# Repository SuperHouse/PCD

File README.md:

PiCAN Display Hat for Raspberry Pi
==================================
Designed by Jonathan Oxer <jon@oxer.com.au>

FEATURES
--------

Supply power via CAN bus, screw terminals, 2.1mm DC jack, or the
PoE header on Raspberry Pi 3 B+. Regulates down to 5V to supply the
Raspberry Pi.

TCAN332 + MCP2515 based CAN bus interface.

0.96" I2C OLED.

INSTALLATION
------------
The design is saved as an EAGLE project. EAGLE PCB design software is
available from www.cadsoftusa.com free for non-commercial use. To use
this project download it and place the directory containing these files
into the "eagle" directory on your computer. Then open EAGLE and
navigate to the project.

DISTRIBUTION
------------
The specific terms of distribution of this project are governed by the
license referenced below.

LICENSE
-------
Licensed under the TAPR Open Hardware License (www.tapr.org/OHL).
The "license" folder within this repository also contains a copy of
this license in plain text format.

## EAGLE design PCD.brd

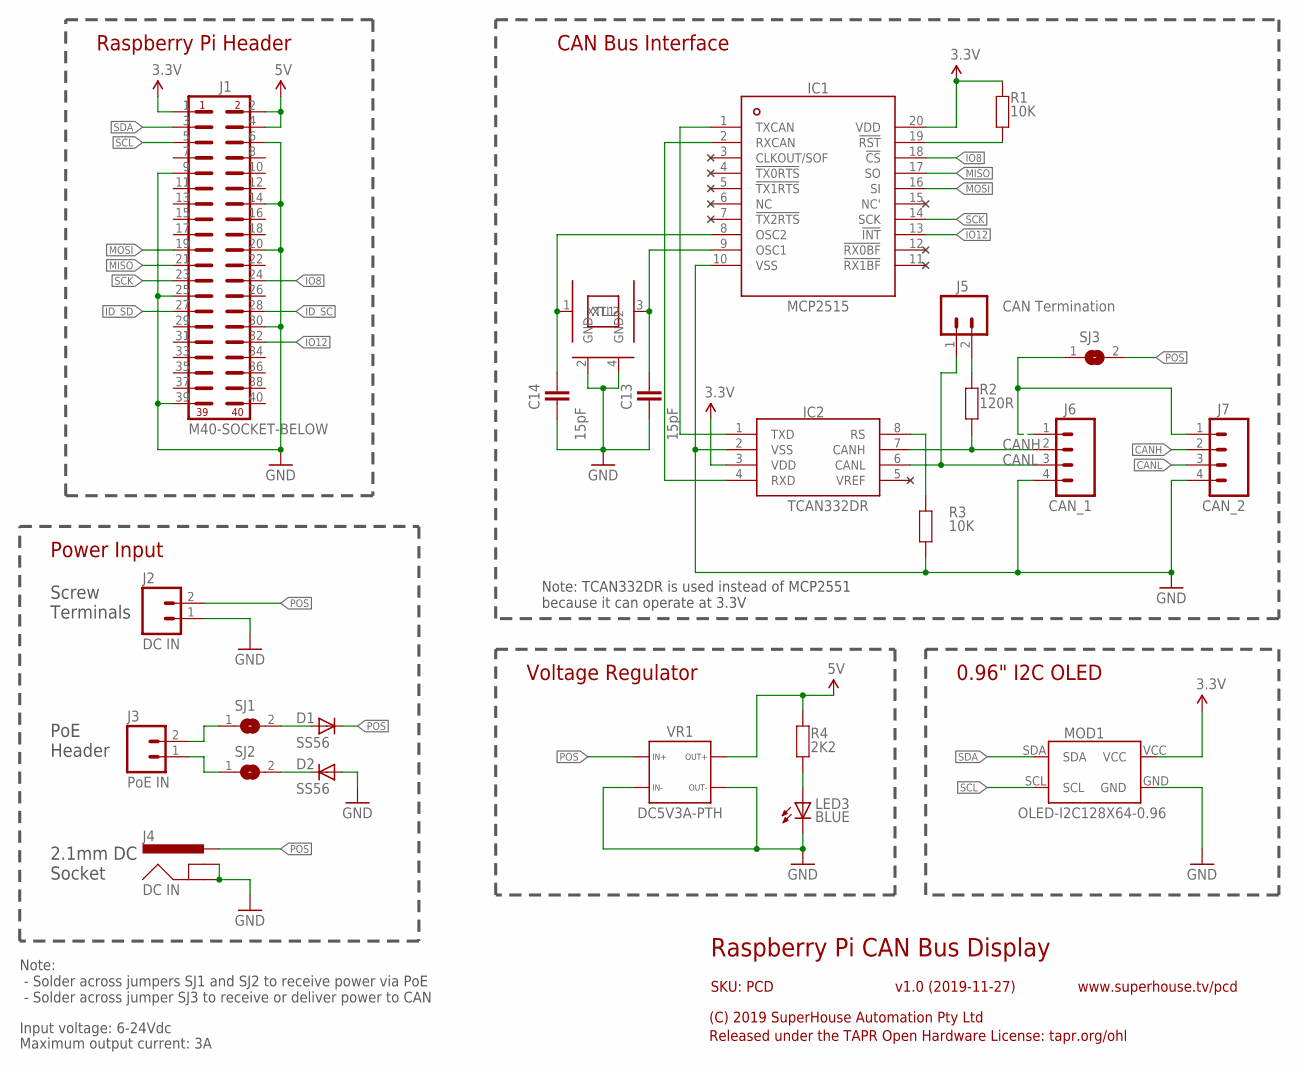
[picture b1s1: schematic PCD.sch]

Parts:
C13, C14: 15pF; C0603
D1, D2: SS56; SMA-DIODE
IC1: MCP2515; TSSOP20
IC2: TCAN332DR; SO08
J1: M40-SOCKET-BELOW; 2X20-S-BELOW
J2: DC IN; SCREWTERMINAL-3.5MM-2
J3: PoE IN; 1X02-S-BELOW
J4: DC IN; POWER_JACK_SLOTS
J5: CAN Termination; 1X02-P
J6: CAN_1; 1X04-P
J7: CAN_2; 1X04-P
LED3: BLUE; LED-0603
MOD1: OLED-I2C128X64-0.96; OLED-128X64-0.96
R1, R3: 10K; R0603
R2: 120R; R0603
R4: 2K2; R0603
SJ1, SJ2, SJ3: SJN; SJ
VR1: DC5V3A-PTH
XTL3: 16MHz; CRYSTAL-SMD-3X2

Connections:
3.3V: IC1.20 (VDD), IC2.3 (VDD), J1.1, MOD1.VCC, R1.2
5V: J1.2, J1.4, R4.1, VR1.3A (3), VR1.3B (3)
CANH: IC2.7 (CANH), J6.2, J7.2, R2.1
CANL: IC2.6 (CANL), J5.1, J6.3, J7.3
CAN_PWR: J6.1, J7.1, SJ3.1
GND: C13.1, C14.1, D2.A, IC1.10 (VSS), IC2.2 (VSS), J1.6, J1.9, J1.14, J1.20, J1.25, J1.30, J1.39, J2.1, J4.GND, J4.GNDBREAK, J6.4, J7.4, LED3.C, MOD1.GND, R3.1, VR1.1A (1), VR1.1B (1), VR1.4A (4), VR1.4B (4), XTL3.2 (GND), XTL3.4 (GND2)
ID_SC: J1.28
ID_SD: J1.27
IO8: IC1.18 (!CS), J1.24
IO12: IC1.13 (!INT), J1.32
MISO: IC1.17 (SO), J1.21
MOSI: IC1.16 (SI), J1.19
unnamed: J3.1, SJ2.1
unnamed: J3.2, SJ1.1
unnamed: J5.2, R2.2
unnamed: D1.A, SJ1.2
unnamed: D2.C, SJ2.2
unnamed: IC2.8 (RS), R3.2
unnamed: IC1.1 (TXCAN), IC2.1 (TXD)
unnamed: IC1.2 (RXCAN), IC2.4 (RXD)
unnamed: C13.2, IC1.9 (OSC1), XTL3.3 (XTL2)
unnamed: C14.2, IC1.8 (OSC2), XTL3.1 (XTL1)
unnamed: IC1.19 (!RST), R1.1
unnamed: LED3.A, R4.2
POS: D1.C, J2.2, J4.PWR, SJ3.2, VR1.2A (2), VR1.2B (2)
SCK: IC1.14 (SCK), J1.23
SCL: J1.5, MOD1.SCL
SDA: J1.3, MOD1.SDA

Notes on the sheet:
Raspberry Pi CAN Bus Display
v1.0 (2019-11-27)
(C) 2019 SuperHouse Automation Pty Ltd
Released under the TAPR Open Hardware License: tapr.org/ohl
www.superhouse.tv/pcd
SKU: PCD
Raspberry Pi Header
Input voltage: 6-24Vdc
Maximum output current: 3A
Screw Terminals
PoE Header
2.1mm DC Socket
Power Input
Voltage Regulator
Note: - Solder across jumpers SJ1 and SJ2 to receive power via PoE - Solder across jumper SJ3 to receive or deliver power to CAN
CAN Bus Interface
Note: TCAN332DR is used instead of MCP2551 because it can operate at 3.3V
0.96" I2C OLED

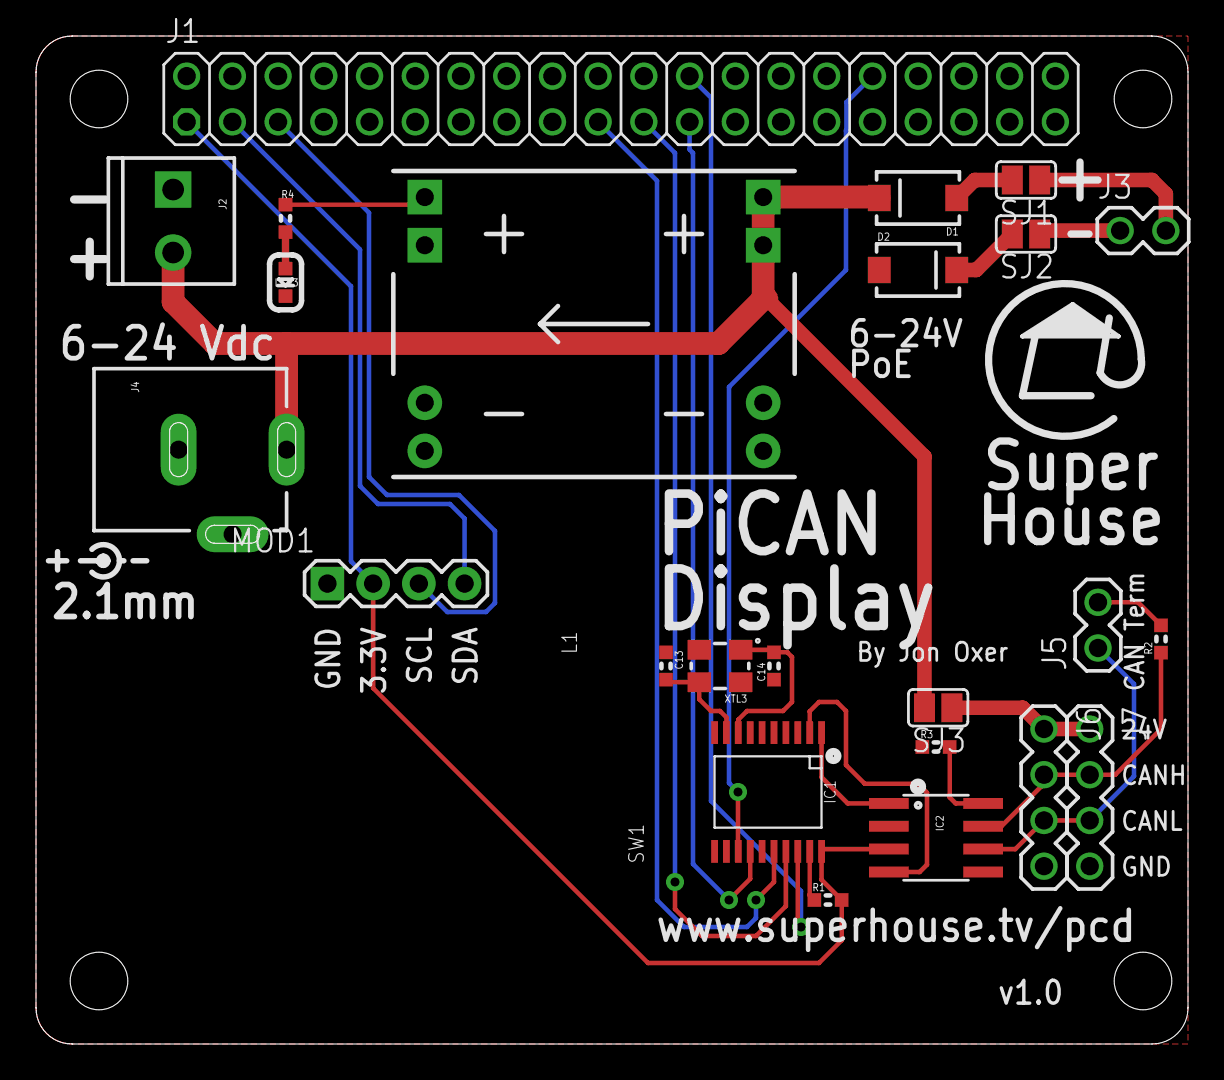
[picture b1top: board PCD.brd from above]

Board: 2 copper layers, 64.0 x 56.0 mm, 24 parts (0 on the bottom side), 26 nets.

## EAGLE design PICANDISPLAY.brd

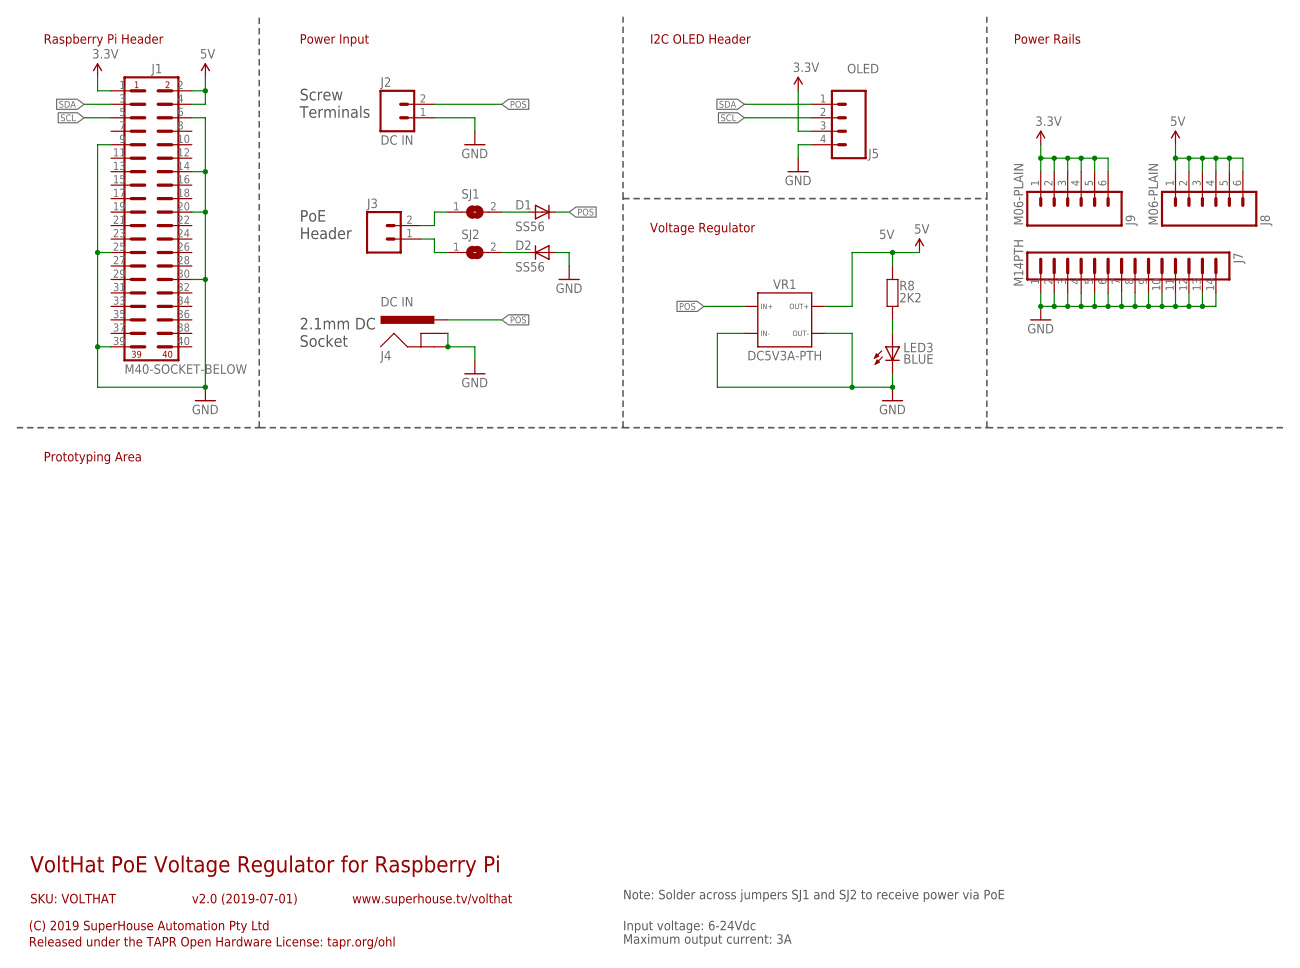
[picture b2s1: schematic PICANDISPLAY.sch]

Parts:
D1, D2: SS56; SMA-DIODE
J1: M40-SOCKET-BELOW; 2X20-S-BELOW
J2: DC IN; SCREWTERMINAL-3.5MM-2
J3: M02-SOCKET-BELOW; 1X02-S-BELOW
J4: DC IN; POWER_JACK_SLOTS
J5: OLED; 1X04
J7: M14PTH; 1X14
J8, J9: M06-PLAIN; 1X06
LED3: BLUE; LED-0603
R8: 2K2; R0603
SJ1, SJ2: SJN; SJ
VR1: DC5V3A-PTH

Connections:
3.3V: J1.1, J5.3, J9.1, J9.2, J9.3, J9.4, J9.5, J9.6
5V: J1.2, J1.4, J8.1, J8.2, J8.3, J8.4, J8.5, J8.6, R8.1, VR1.3A (3), VR1.3B (3)
GND: D2.A, J1.6, J1.9, J1.14, J1.20, J1.25, J1.30, J1.39, J2.1, J4.GND, J4.GNDBREAK, J5.4, J7.1 (14), J7.2 (13), J7.3 (12), J7.4 (11), J7.5 (10), J7.6 (9), J7.7 (8), J7.8 (7), J7.9 (6), J7.10 (5), J7.11 (4), J7.12 (3), J7.13 (2), J7.14 (1), LED3.C, VR1.1A (1), VR1.1B (1), VR1.4A (4), VR1.4B (4)
unnamed: J3.1, SJ2.1
unnamed: J3.2, SJ1.1
unnamed: D1.A, SJ1.2
unnamed: D2.C, SJ2.2
unnamed: LED3.A, R8.2
POS: D1.C, J2.2, J4.PWR, VR1.2A (2), VR1.2B (2)
SCL: J1.5, J5.2
SDA: J1.3, J5.1

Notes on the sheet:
VoltHat PoE Voltage Regulator for Raspberry Pi
v2.0 (2019-07-01)
(C) 2019 SuperHouse Automation Pty Ltd
Released under the TAPR Open Hardware License: tapr.org/ohl
www.superhouse.tv/volthat
SKU: VOLTHAT
Raspberry Pi Header
Input voltage: 6-24Vdc
Maximum output current: 3A
Screw Terminals
PoE Header
2.1mm DC Socket
Power Input
I2C OLED Header
Power Rails
Prototyping Area
Voltage Regulator
Note: Solder across jumpers SJ1 and SJ2 to receive power via PoE

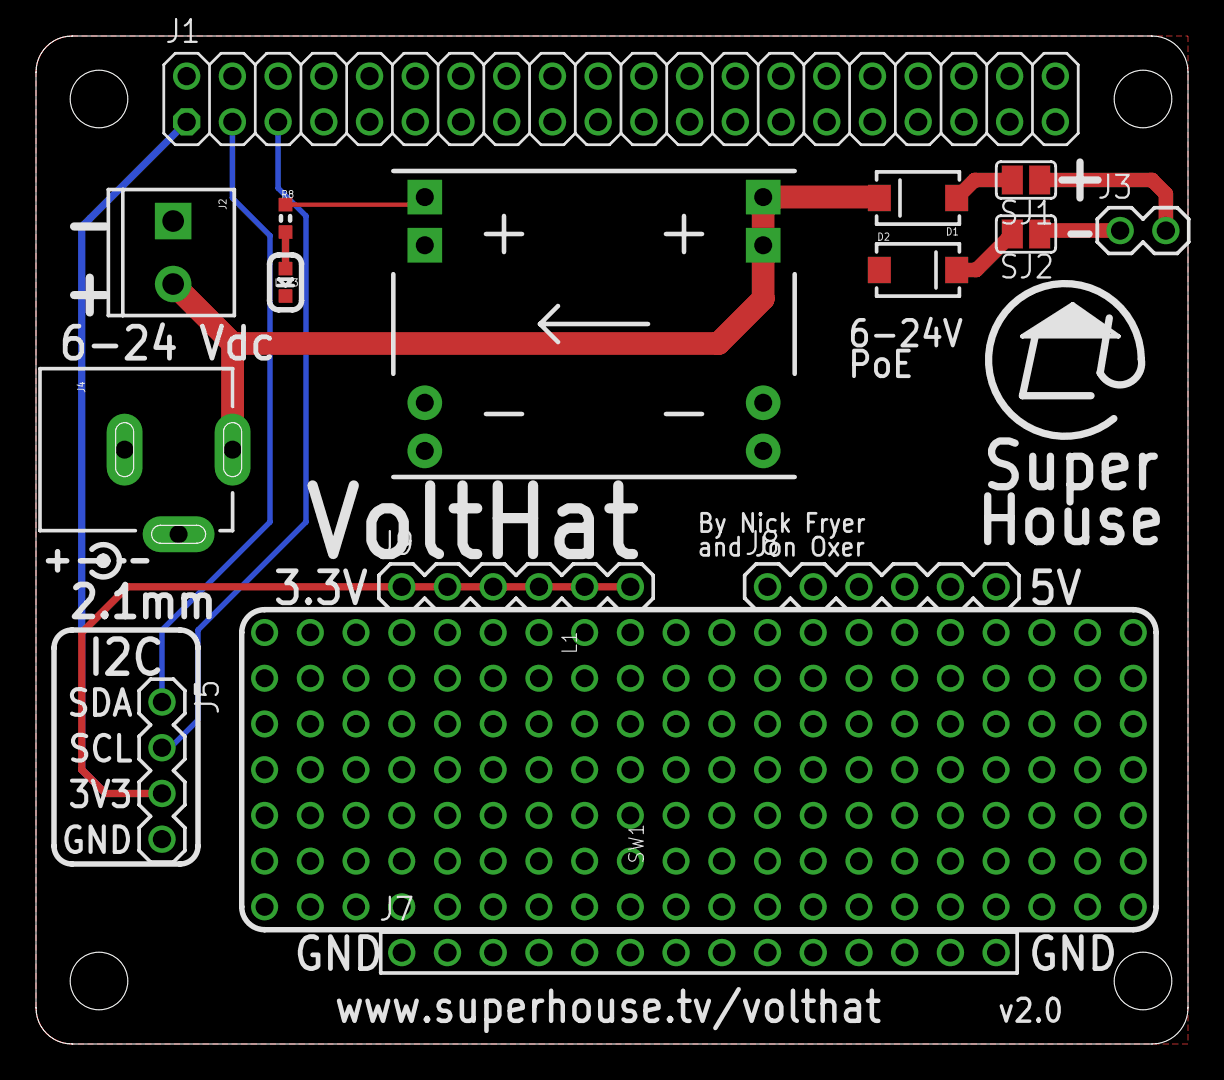
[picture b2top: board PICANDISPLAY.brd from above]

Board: 2 copper layers, 64.0 x 56.0 mm, 15 parts (0 on the bottom side), 11 nets.

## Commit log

2019-11-20 Renamed files from original project
2019-11-20 Basic schematic and routing. Time to ponder it for a while.
2019-11-20 Silkscreen and docs
2019-11-20 Added nets for HAT EEPROM
2020-03-18 Major work for v1.0 release

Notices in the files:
PCD.brd:
Copyright 2019 SuperHouse Automation Pty Ltd
